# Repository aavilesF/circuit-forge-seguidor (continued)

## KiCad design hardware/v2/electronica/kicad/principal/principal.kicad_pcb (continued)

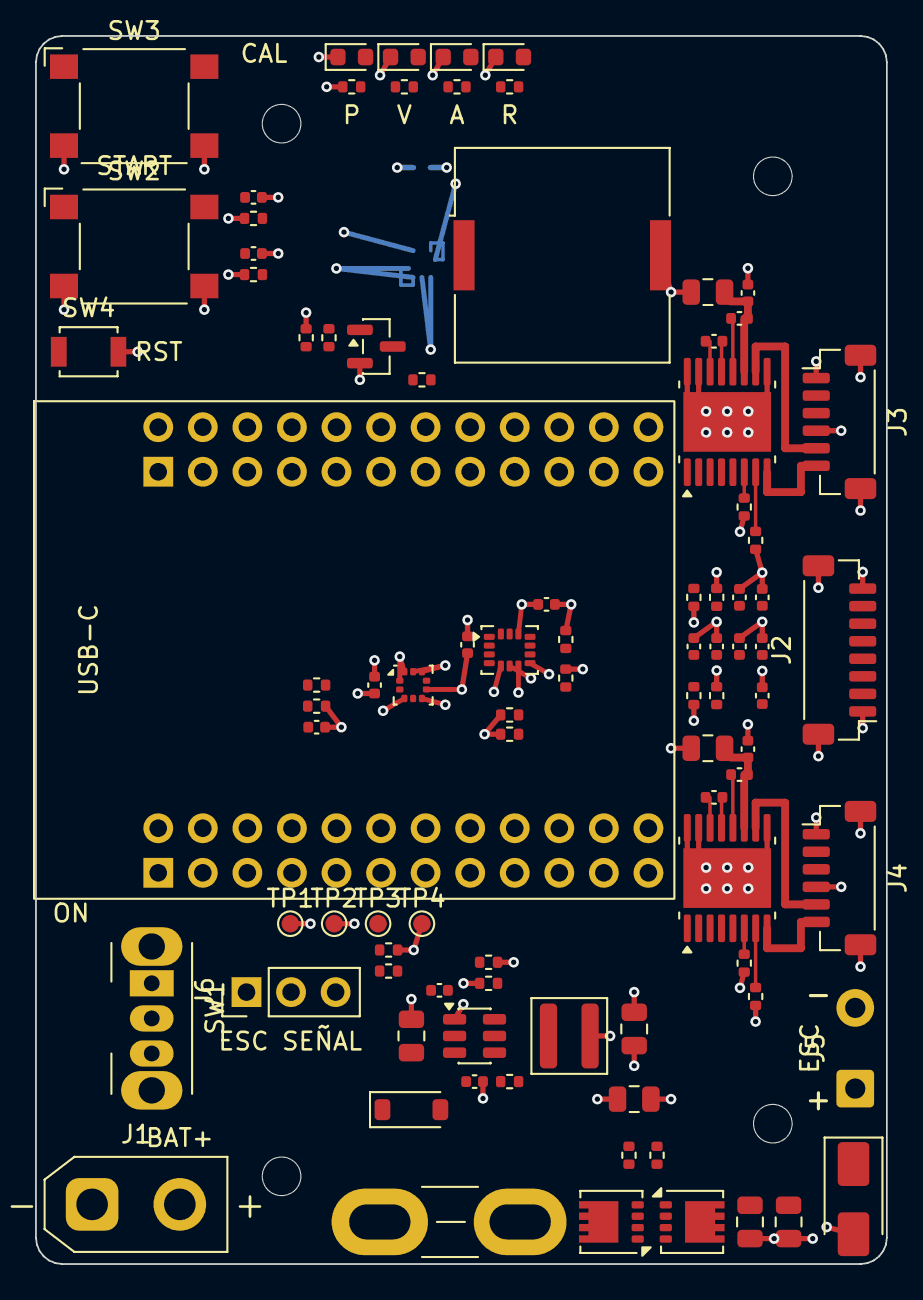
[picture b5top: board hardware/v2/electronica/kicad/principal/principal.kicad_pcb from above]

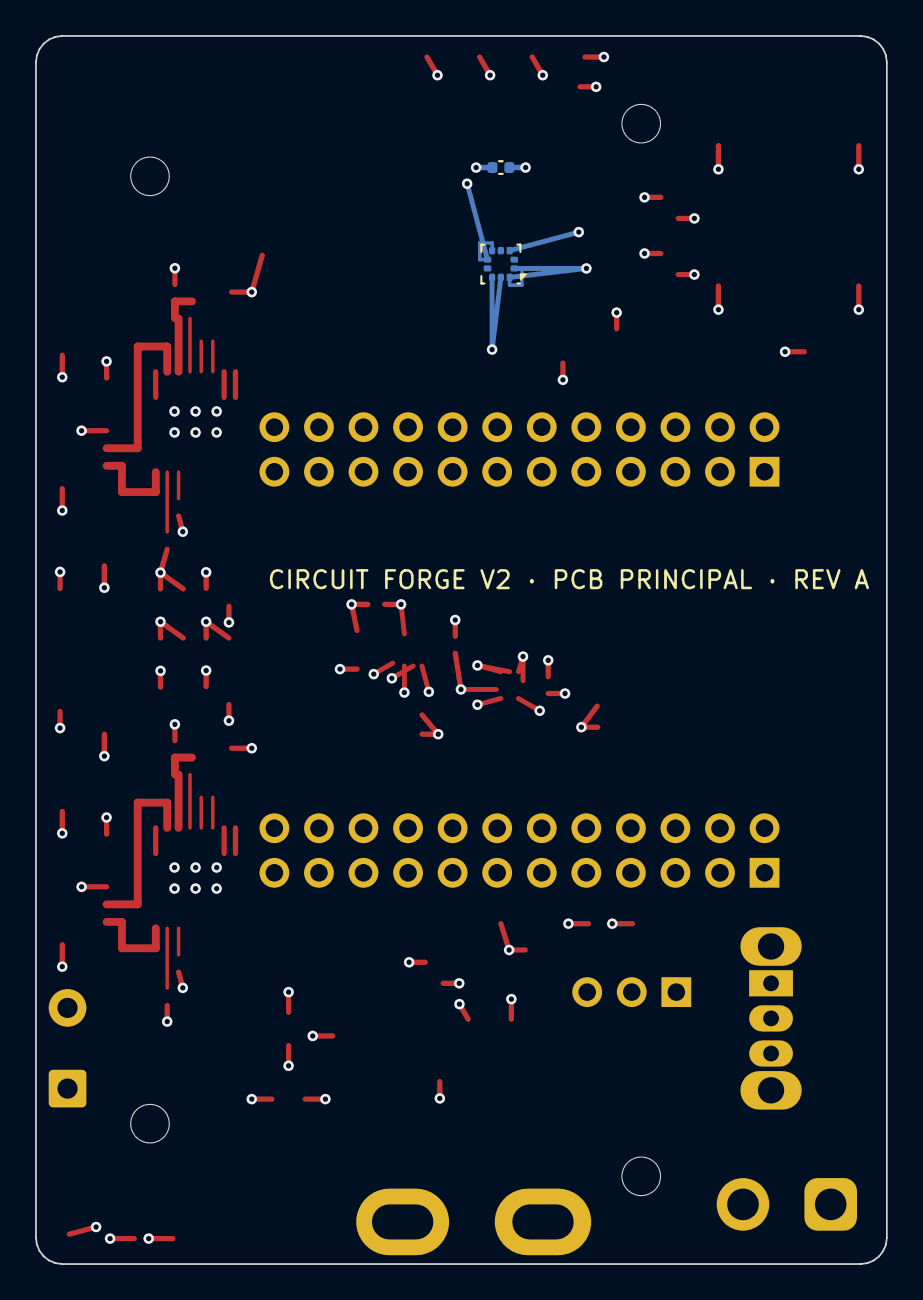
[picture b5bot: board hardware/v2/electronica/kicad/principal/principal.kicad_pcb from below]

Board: 4 copper layers, 48.5 x 70.0 mm, 96 parts (2 on the bottom side), 64 nets.

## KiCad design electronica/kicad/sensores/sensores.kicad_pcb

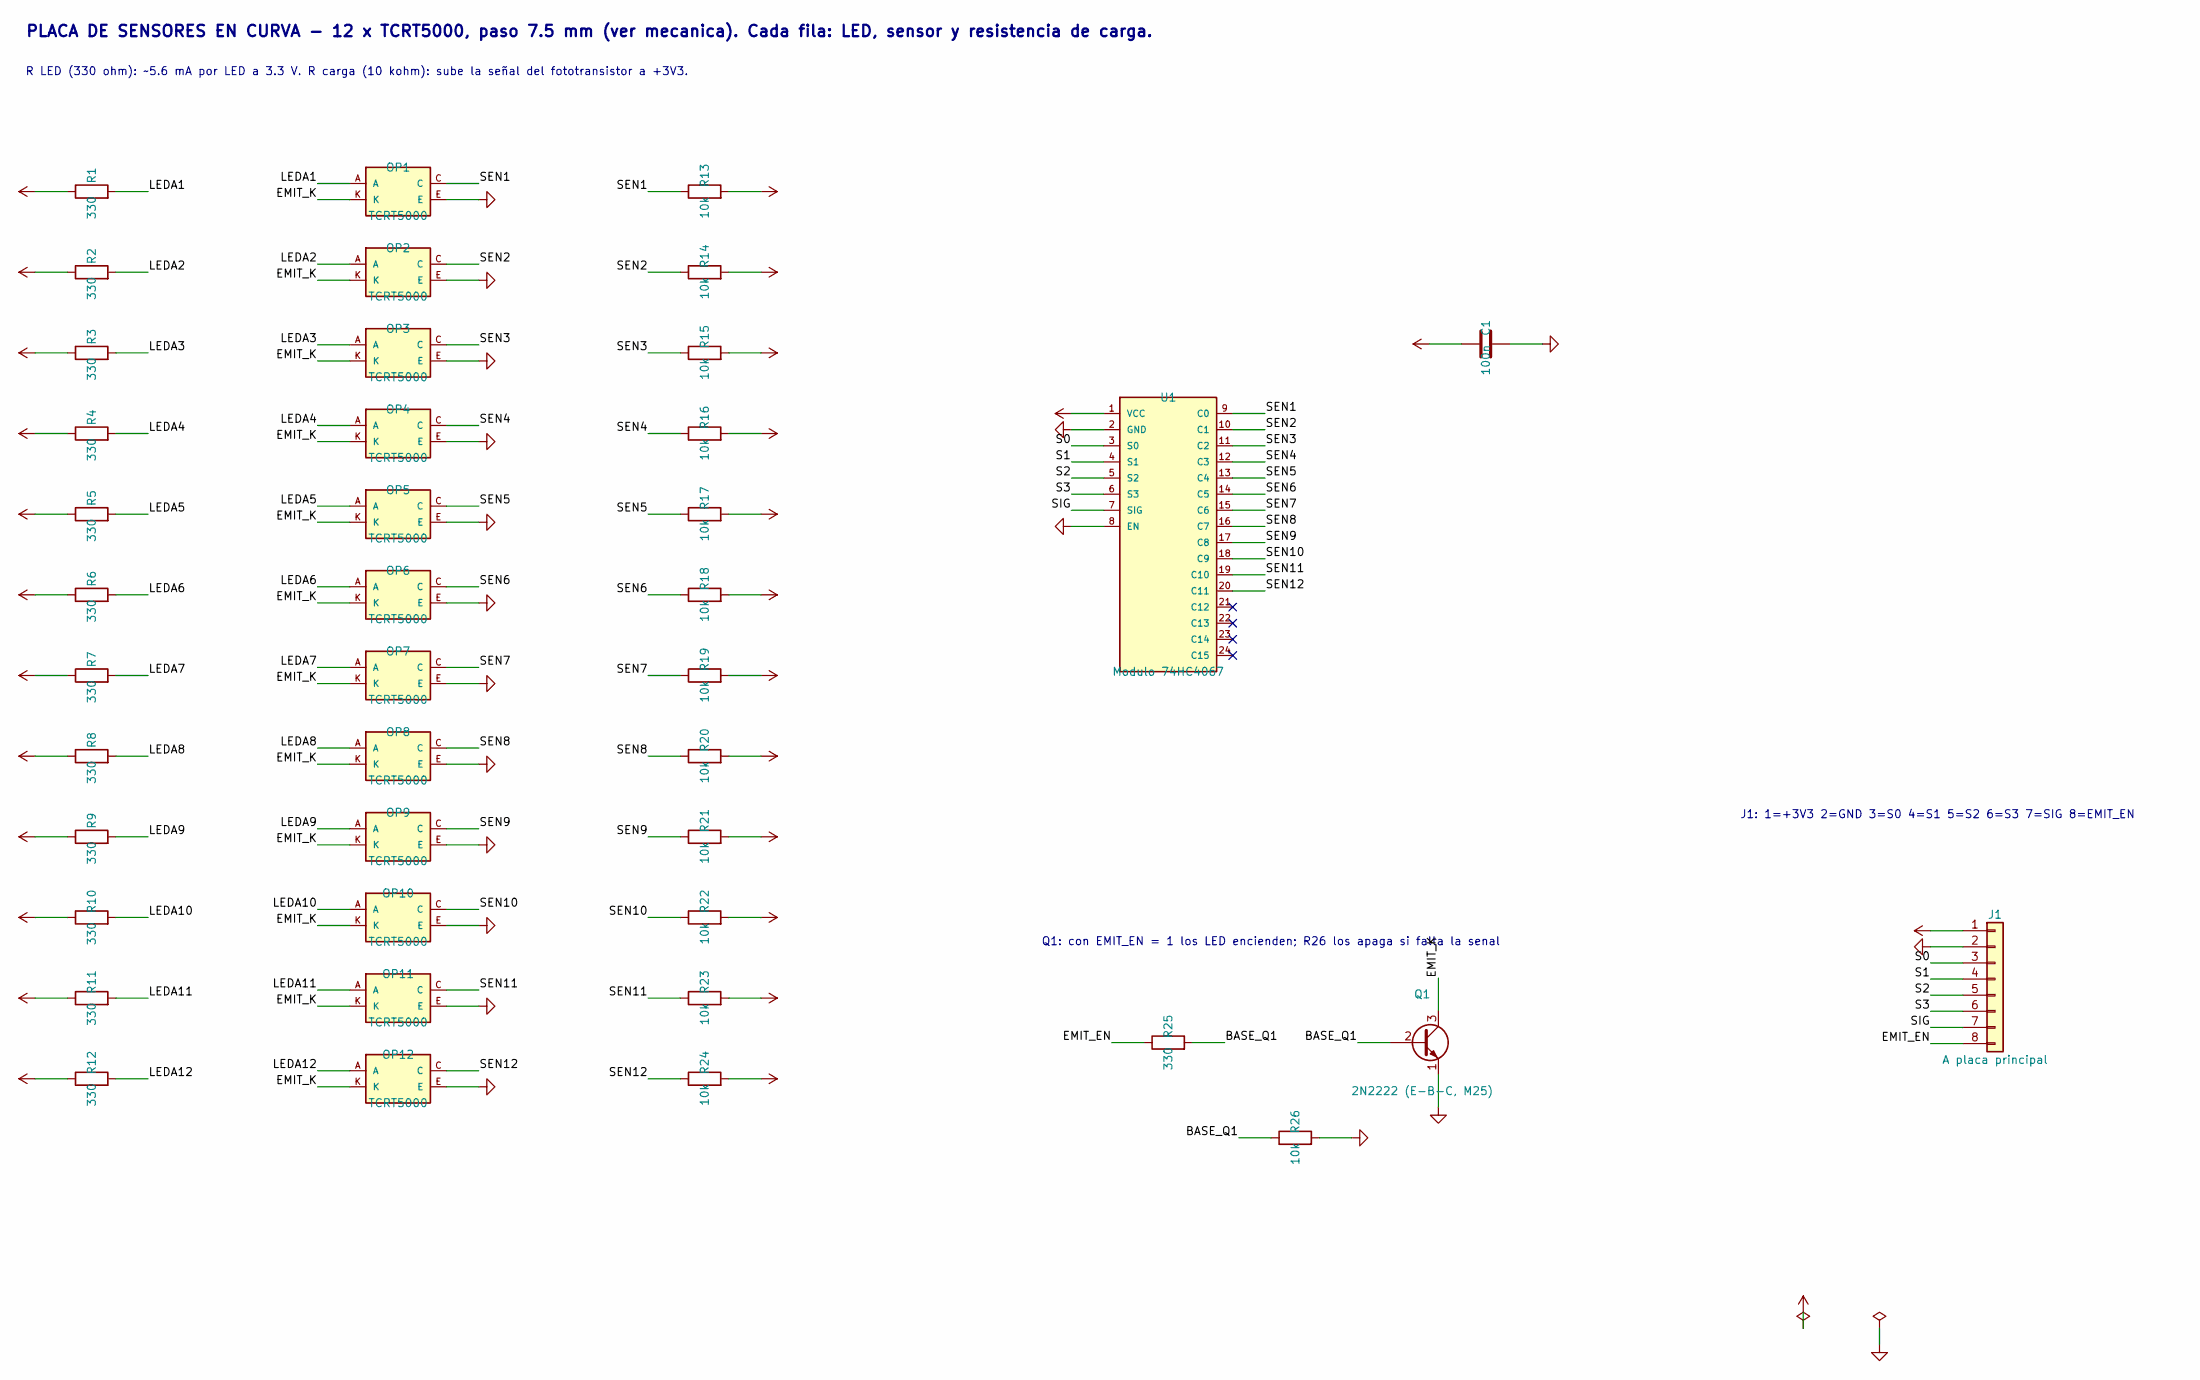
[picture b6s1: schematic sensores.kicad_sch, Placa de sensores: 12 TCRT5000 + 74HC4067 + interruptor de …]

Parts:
C1: 100n; C_Disc_D5.0mm_W2.5mm_P5.00mm
J1: A placa principal; PinHeader_1x08_P2.54mm_Vertical
OP1, OP2, OP3, OP4, OP5, OP6, OP7, OP8, OP9, OP10, OP11, OP12: TCRT5000; TCRT5000_THT
Q1: 2N2222 (E-B-C, M25); TO-92_Inline_Wide
R1, R2, R3, R4, R5, R6, R7, R8, R9, R10, R11, R12, R25: 330; R_Axial_DIN0207_L6.3mm_D2.5mm_P2.54mm_Vertical
R13, R14, R15, R16, R17, R18, R19, R20, R21, R22, R23, R24, R26: 10k; R_Axial_DIN0207_L6.3mm_D2.5mm_P2.54mm_Vertical
U1: Modulo 74HC4067; Modulo_MUX4067_VERIFICAR

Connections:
+3V3: C1.1, J1.1, R1.1, R2.1, R3.1, R4.1, R5.1, R6.1, R7.1, R8.1, R9.1, R10.1, R11.1, R12.1, R13.2, R14.2, R15.2, R16.2, R17.2, R18.2, R19.2, R20.2, R21.2, R22.2, R23.2, R24.2, U1.1 (VCC)
/BASE_Q1: Q1.2 (B), R25.2, R26.1
/EMIT_EN: J1.8, R25.1
/EMIT_K: OP1.K, OP2.K, OP3.K, OP4.K, OP5.K, OP6.K, OP7.K, OP8.K, OP9.K, OP10.K, OP11.K, OP12.K, Q1.3 (C)
/LEDA1: OP1.A, R1.2
/LEDA2: OP2.A, R2.2
/LEDA3: OP3.A, R3.2
/LEDA4: OP4.A, R4.2
/LEDA5: OP5.A, R5.2
/LEDA6: OP6.A, R6.2
/LEDA7: OP7.A, R7.2
/LEDA8: OP8.A, R8.2
/LEDA9: OP9.A, R9.2
/LEDA10: OP10.A, R10.2
/LEDA11: OP11.A, R11.2
/LEDA12: OP12.A, R12.2
/S0: J1.3, U1.3 (S0)
/S1: J1.4, U1.4 (S1)
/S2: J1.5, U1.5 (S2)
/S3: J1.6, U1.6 (S3)
/SEN1: OP1.C, R13.1, U1.9 (C0)
/SEN2: OP2.C, R14.1, U1.10 (C1)
/SEN3: OP3.C, R15.1, U1.11 (C2)
/SEN4: OP4.C, R16.1, U1.12 (C3)
/SEN5: OP5.C, R17.1, U1.13 (C4)
/SEN6: OP6.C, R18.1, U1.14 (C5)
/SEN7: OP7.C, R19.1, U1.15 (C6)
/SEN8: OP8.C, R20.1, U1.16 (C7)
/SEN9: OP9.C, R21.1, U1.17 (C8)
/SEN10: OP10.C, R22.1, U1.18 (C9)
/SEN11: OP11.C, R23.1, U1.19 (C10)
/SEN12: OP12.C, R24.1, U1.20 (C11)
/SIG: J1.7, U1.7 (SIG)
GND: C1.2, J1.2, OP1.E, OP2.E, OP3.E, OP4.E, OP5.E, OP6.E, OP7.E, OP8.E, OP9.E, OP10.E, OP11.E, OP12.E, Q1.1 (E), R26.2, U1.2 (GND), U1.8 (EN)

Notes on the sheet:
PLACA DE SENSORES EN CURVA - 12 x TCRT5000, paso 7.5 mm (ver mecanica). Cada fila: LED, sensor y resistencia de carga.
R LED (330 ohm): ~5.6 mA por LED a 3.3 V. R carga (10 kohm): sube la señal del fototransistor a +3V3.
Q1: con EMIT_EN = 1 los LED encienden; R26 los apaga si falta la senal
J1: 1=+3V3 2=GND 3=S0 4=S1 5=S2 6=S3 7=SIG 8=EMIT_EN

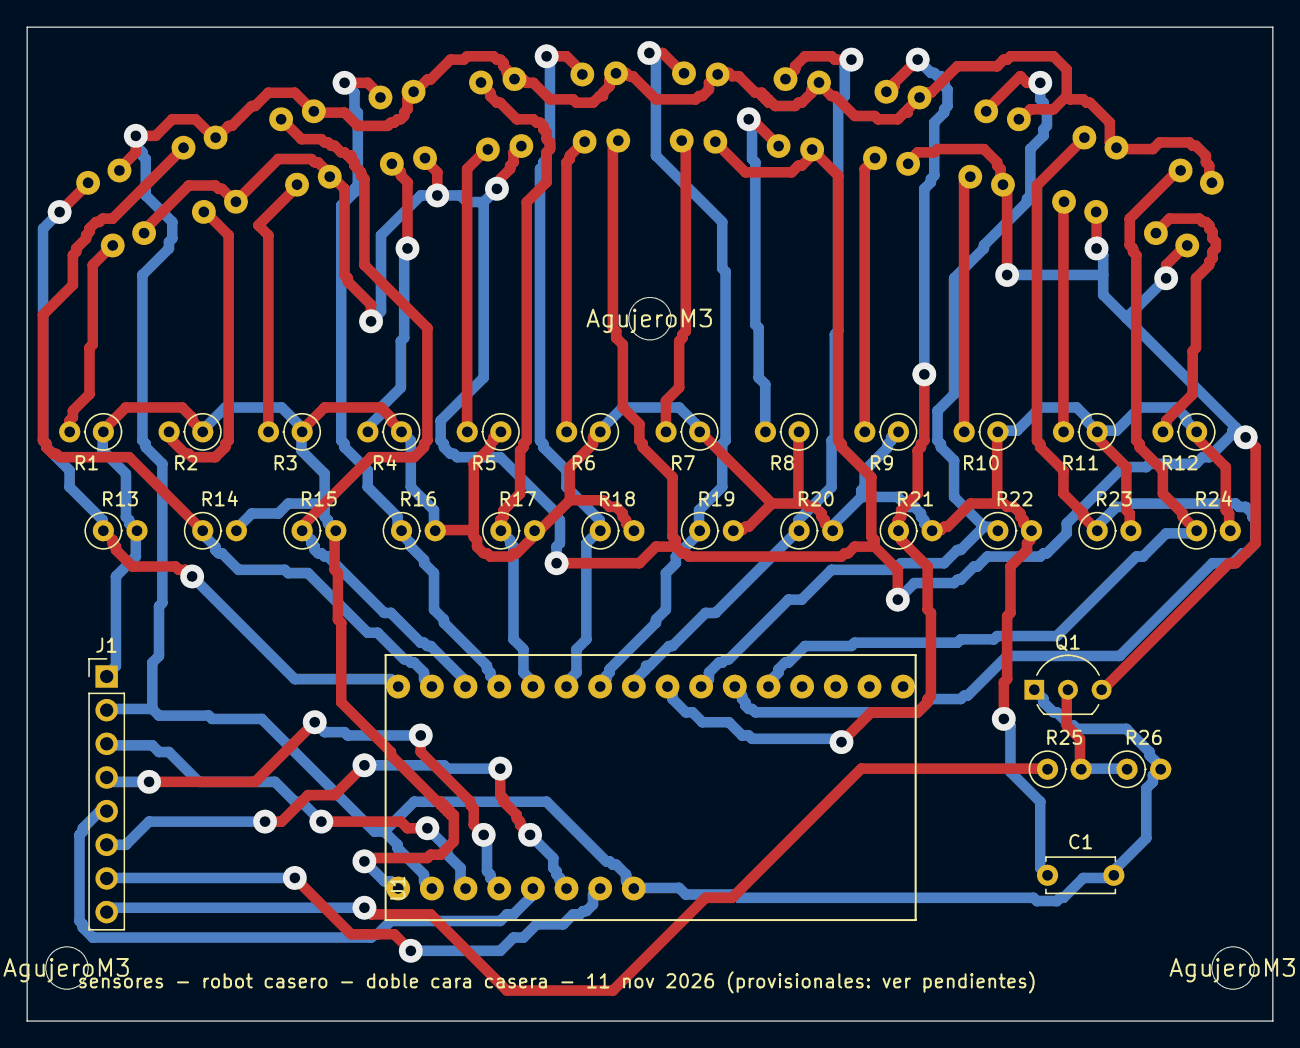
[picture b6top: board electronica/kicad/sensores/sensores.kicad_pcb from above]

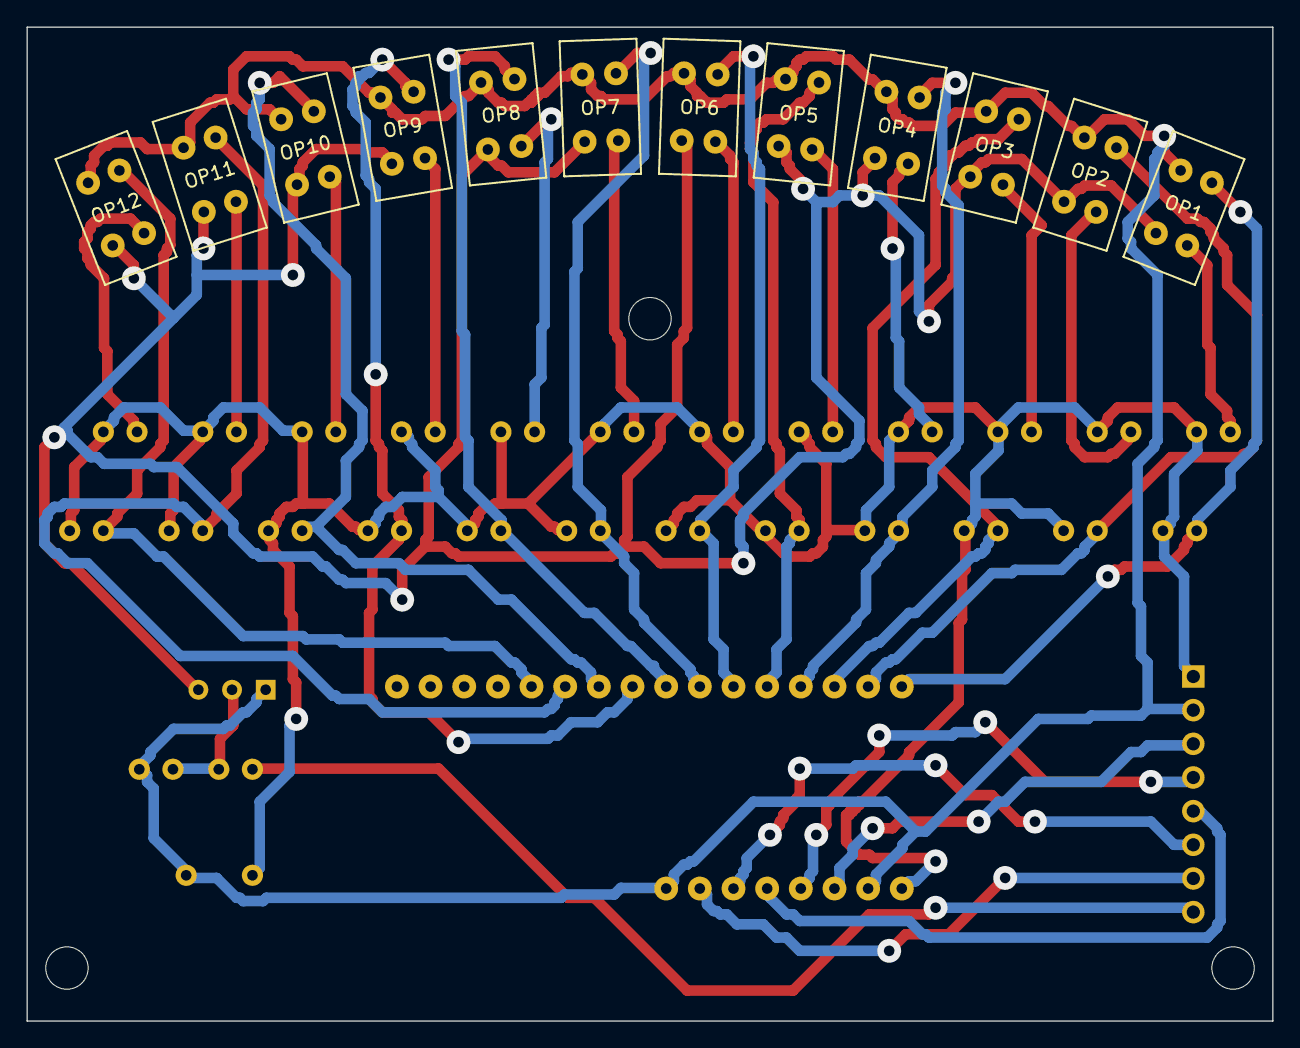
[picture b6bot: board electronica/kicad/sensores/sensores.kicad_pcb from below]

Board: 2 copper layers, 94.0 x 75.0 mm, 45 parts (12 on the bottom side), 34 nets.

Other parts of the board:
H1, H2, H3: AgujeroM3

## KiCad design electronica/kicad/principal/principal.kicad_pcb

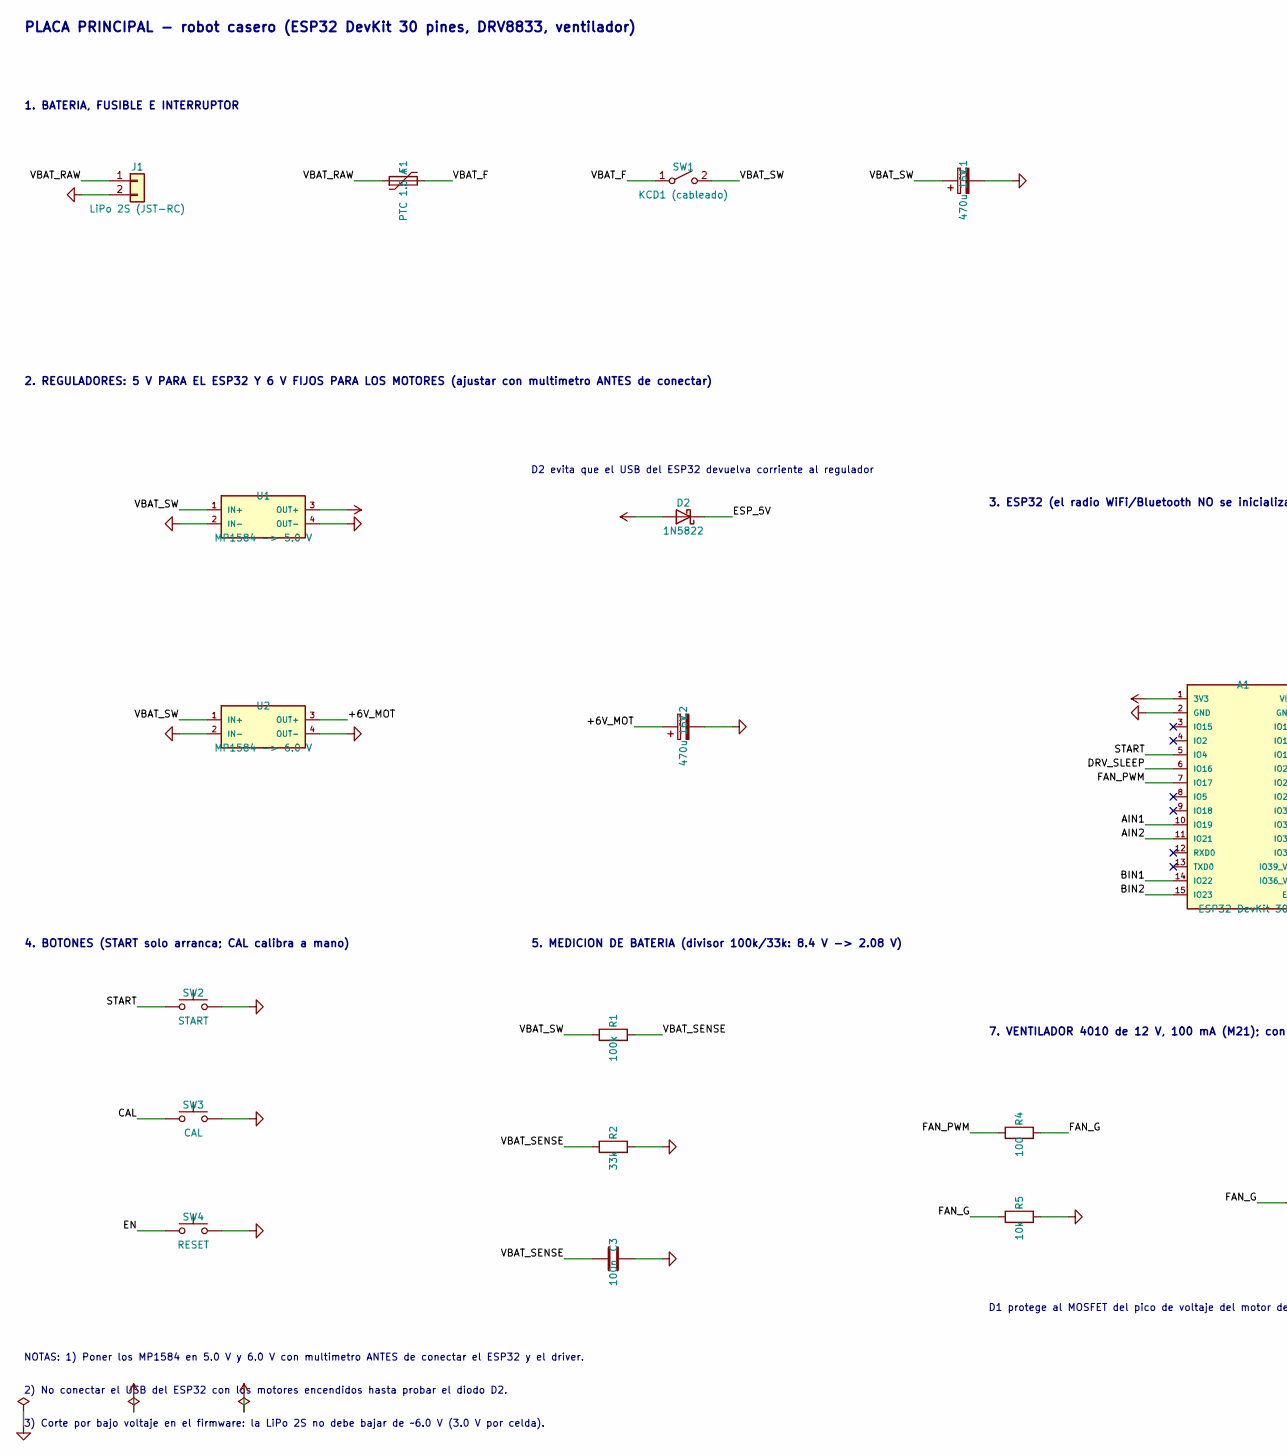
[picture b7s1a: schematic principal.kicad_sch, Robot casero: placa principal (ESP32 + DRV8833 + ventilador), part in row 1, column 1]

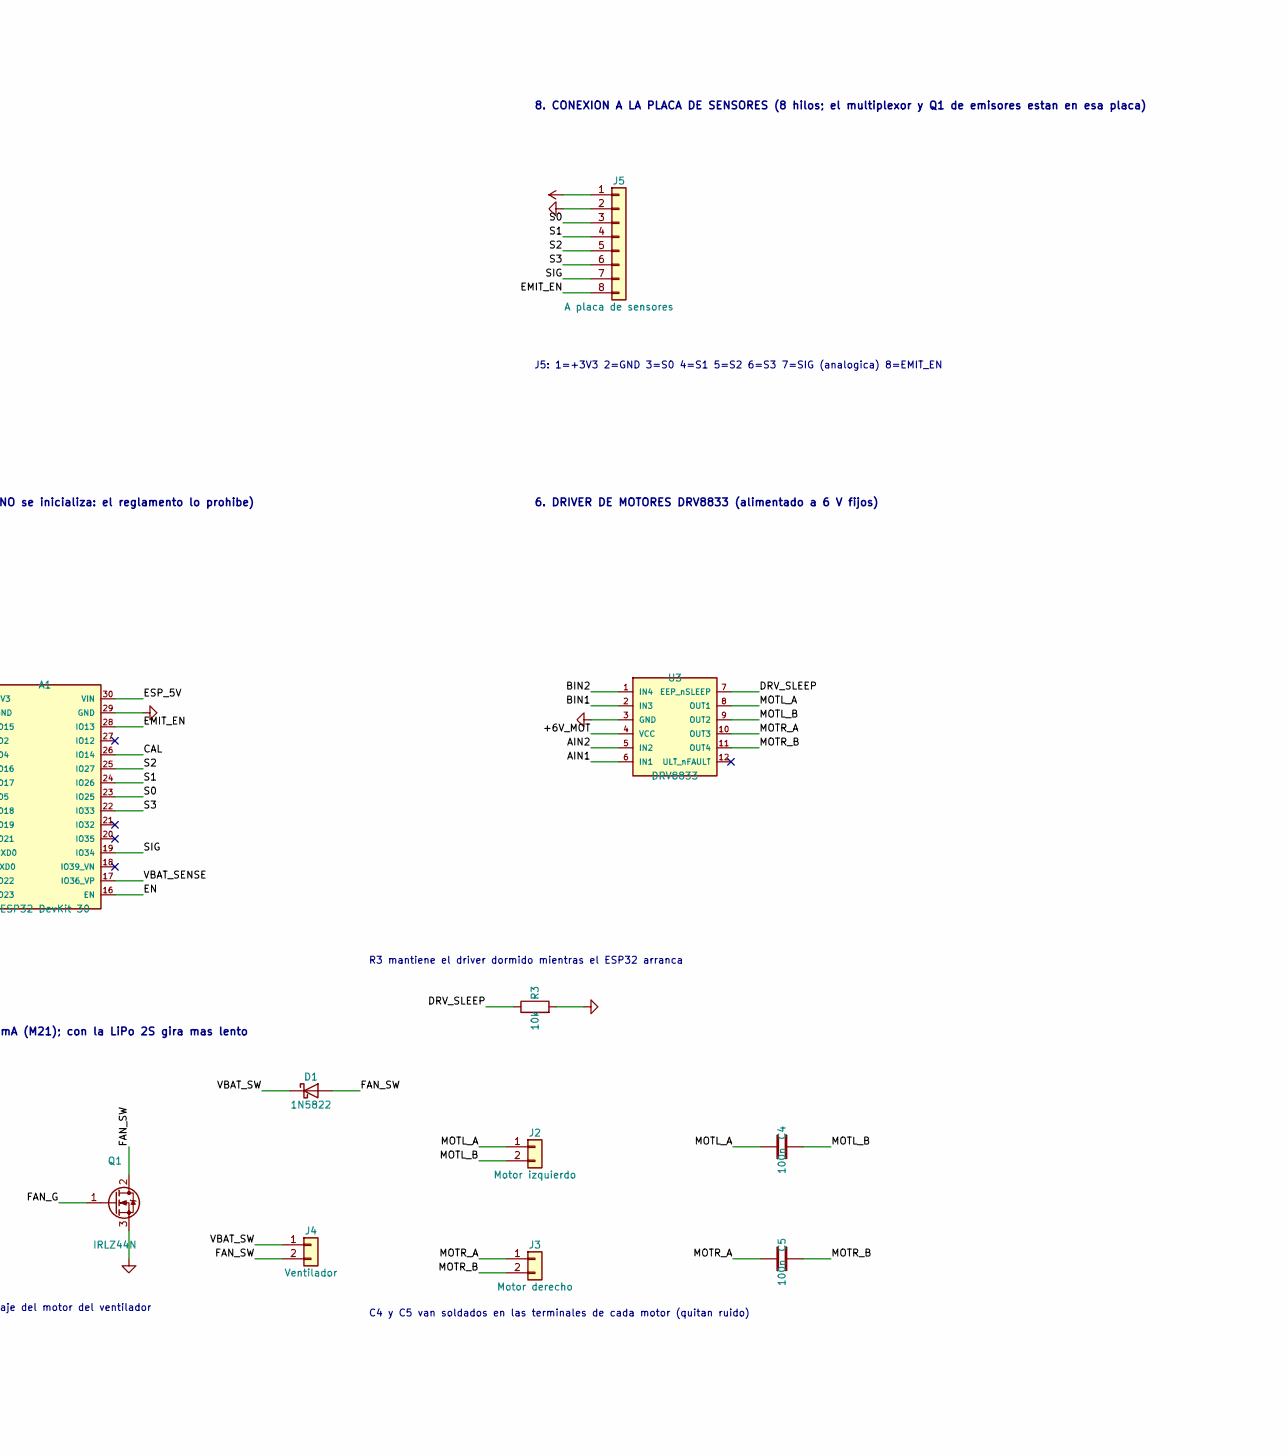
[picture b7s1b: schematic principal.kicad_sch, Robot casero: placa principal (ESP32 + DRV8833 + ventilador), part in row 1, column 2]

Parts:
A1: ESP32 DevKit 30; ESP32_DevKit_30
C1, C2: 470u 16V; CP_Radial_D8.0mm_P3.80mm
C3, C4, C5: 100n; C_Disc_D7.5mm_W5.0mm_P5.00mm
D1, D2: 1N5822; D_DO-201AD_P20.32mm_Taladro1.3
F1: PTC 1.5 A; PTC_Radial_VERIFICAR
J1: LiPo 2S (JST-RC); PinHeader_1x02_P2.54mm_Vertical
J2: Motor izquierdo; PinHeader_1x02_P2.54mm_Vertical
J3: Motor derecho; PinHeader_1x02_P2.54mm_Vertical
J4: Ventilador; PinHeader_1x02_P2.54mm_Vertical
J5: A placa de sensores; PinHeader_1x08_P2.54mm_Vertical
Q1: IRLZ44N; TO-220-3_Vertical
R1: 100k; R_Axial_DIN0207_L6.3mm_D2.5mm_P7.62mm_Horizontal
R2: 33k; R_Axial_DIN0207_L6.3mm_D2.5mm_P7.62mm_Horizontal
R3, R5: 10k; R_Axial_DIN0207_L6.3mm_D2.5mm_P7.62mm_Horizontal
R4: 100; R_Axial_DIN0207_L6.3mm_D2.5mm_P7.62mm_Horizontal
SW1: KCD1 (cableado); PinHeader_1x02_P2.54mm_Vertical
SW2: START; SW_PUSH-12mm
SW3: CAL; SW_PUSH_6mm
SW4: RESET; SW_PUSH_6mm
U1: MP1584 -> 5.0 V; Modulo_MP1584
U2: MP1584 -> 6.0 V; Modulo_MP1584
U3: DRV8833; Modulo_DRV8833

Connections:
+3V3: A1.1 (3V3), J5.1
+5V: D2.2 (A), U1.3 (OUT+)
/+6V_MOT: C2.1, U2.3 (OUT+), U3.4 (VCC)
/AIN1: A1.10 (IO19), U3.6 (IN1)
/AIN2: A1.11 (IO21), U3.5 (IN2)
/BIN1: A1.14 (IO22), U3.2 (IN3)
/BIN2: A1.15 (IO23), U3.1 (IN4)
/CAL: A1.26 (IO14), SW3.1
/DRV_SLEEP: A1.6 (IO16), R3.1, U3.7 (EEP_nSLEEP)
/EMIT_EN: A1.28 (IO13), J5.8
/EN: A1.16 (EN), SW4.1
/ESP_5V: A1.30 (VIN), D2.1 (K)
/FAN_G: Q1.1 (G), R4.2, R5.1
/FAN_PWM: A1.7 (IO17), R4.1
/FAN_SW: D1.2 (A), J4.2, Q1.2 (D)
/MOTL_A: C4.1, J2.1, U3.8 (OUT1)
/MOTL_B: C4.2, J2.2, U3.9 (OUT2)
/MOTR_A: C5.1, J3.1, U3.10 (OUT3)
/MOTR_B: C5.2, J3.2, U3.11 (OUT4)
/S0: A1.23 (IO25), J5.3
/S1: A1.24 (IO26), J5.4
/S2: A1.25 (IO27), J5.5
/S3: A1.22 (IO33), J5.6
/SIG: A1.19 (IO34), J5.7
/START: A1.5 (IO4), SW2.1
/VBAT_F: F1.2, SW1.1 (A)
/VBAT_RAW: F1.1, J1.1
/VBAT_SENSE: A1.17 (IO36_VP), C3.1, R1.2, R2.1
/VBAT_SW: C1.1, D1.1 (K), J4.1, R1.1, SW1.2 (B), U1.1 (IN+), U2.1 (IN+)
GND: A1.2 (GND), A1.29 (GND), C1.2, C2.2, C3.2, J1.2, J5.2, Q1.3 (S), R2.2, R3.2, R5.2, SW2.2, SW3.2, SW4.2, U1.2 (IN-), U1.4 (OUT-), U2.2 (IN-), U2.4 (OUT-), U3.3 (GND)

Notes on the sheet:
PLACA PRINCIPAL - robot casero (ESP32 DevKit 30 pines, DRV8833, ventilador)
1. BATERIA, FUSIBLE E INTERRUPTOR
2. REGULADORES: 5 V PARA EL ESP32 Y 6 V FIJOS PARA LOS MOTORES (ajustar con multimetro ANTES de conectar)
D2 evita que el USB del ESP32 devuelva corriente al regulador
3. ESP32 (el radio WiFi/Bluetooth NO se inicializa: el reglamento lo prohibe)
4. BOTONES (START solo arranca; CAL calibra a mano)
5. MEDICION DE BATERIA (divisor 100k/33k: 8.4 V -> 2.08 V)
6. DRIVER DE MOTORES DRV8833 (alimentado a 6 V fijos)
R3 mantiene el driver dormido mientras el ESP32 arranca
C4 y C5 van soldados en las terminales de cada motor (quitan ruido)
7. VENTILADOR 4010 de 12 V, 100 mA (M21); con la LiPo 2S gira mas lento
D1 protege al MOSFET del pico de voltaje del motor del ventilador
8. CONEXION A LA PLACA DE SENSORES (8 hilos; el multiplexor y Q1 de emisores estan en esa placa)
J5: 1=+3V3 2=GND 3=S0 4=S1 5=S2 6=S3 7=SIG (analogica) 8=EMIT_EN
NOTAS: 1) Poner los MP1584 en 5.0 V y 6.0 V con multimetro ANTES de conectar el ESP32 y el driver.
2) No conectar el USB del ESP32 con los motores encendidos hasta probar el diodo D2.
3) Corte por bajo voltaje en el firmware: la LiPo 2S no debe bajar de ~6.0 V (3.0 V por celda).

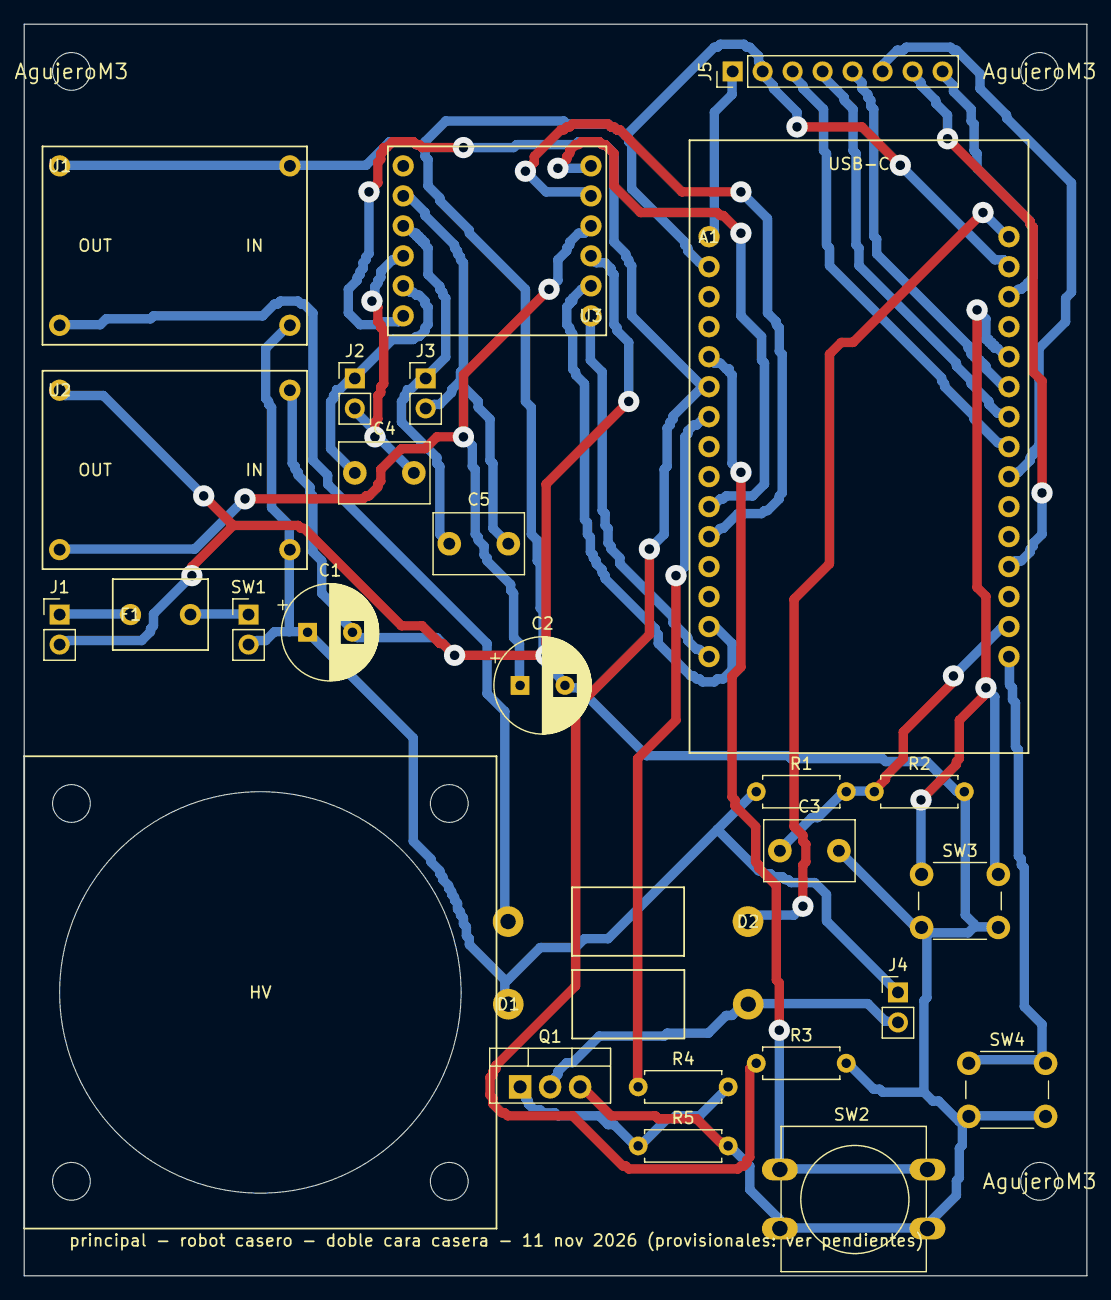
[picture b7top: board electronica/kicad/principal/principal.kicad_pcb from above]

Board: 2 copper layers, 90.0 x 106.0 mm, 31 parts (0 on the bottom side), 30 nets.

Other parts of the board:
H1, H2, H3: AgujeroM3
HV: Hueco ventilador; Hueco_Ventilador_34mm

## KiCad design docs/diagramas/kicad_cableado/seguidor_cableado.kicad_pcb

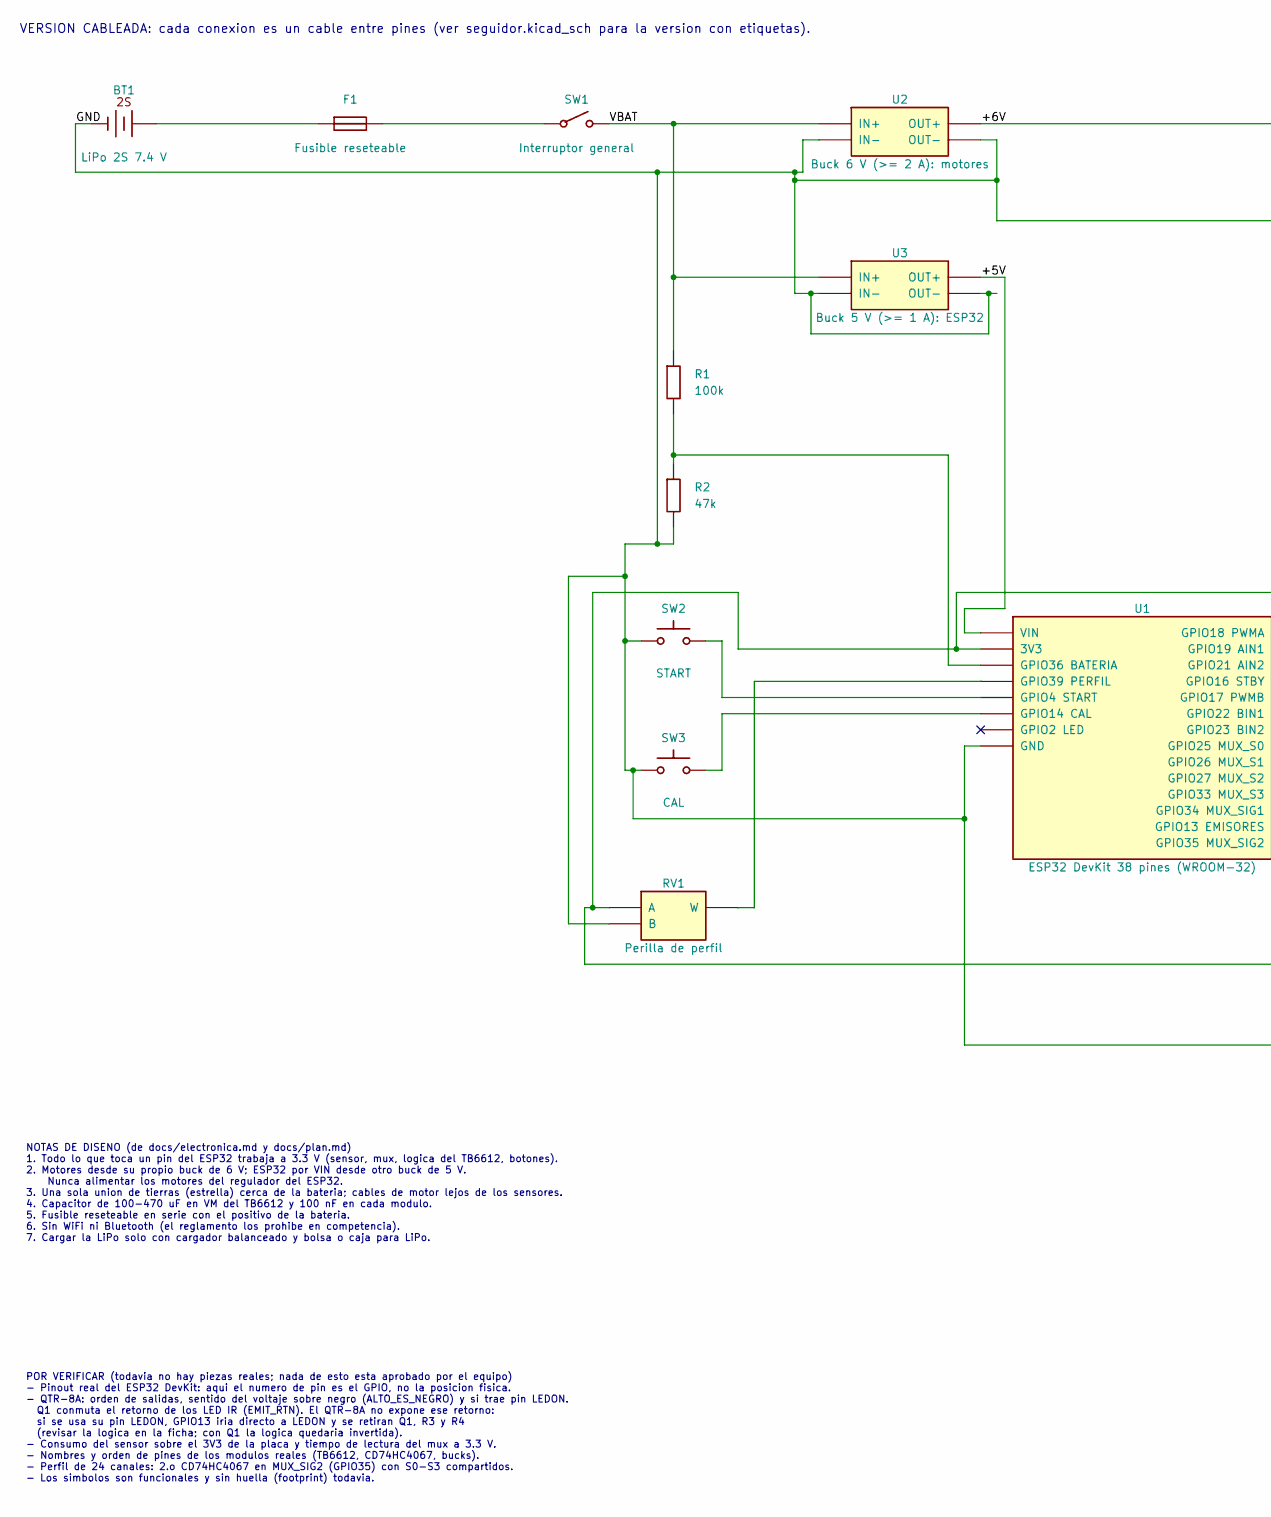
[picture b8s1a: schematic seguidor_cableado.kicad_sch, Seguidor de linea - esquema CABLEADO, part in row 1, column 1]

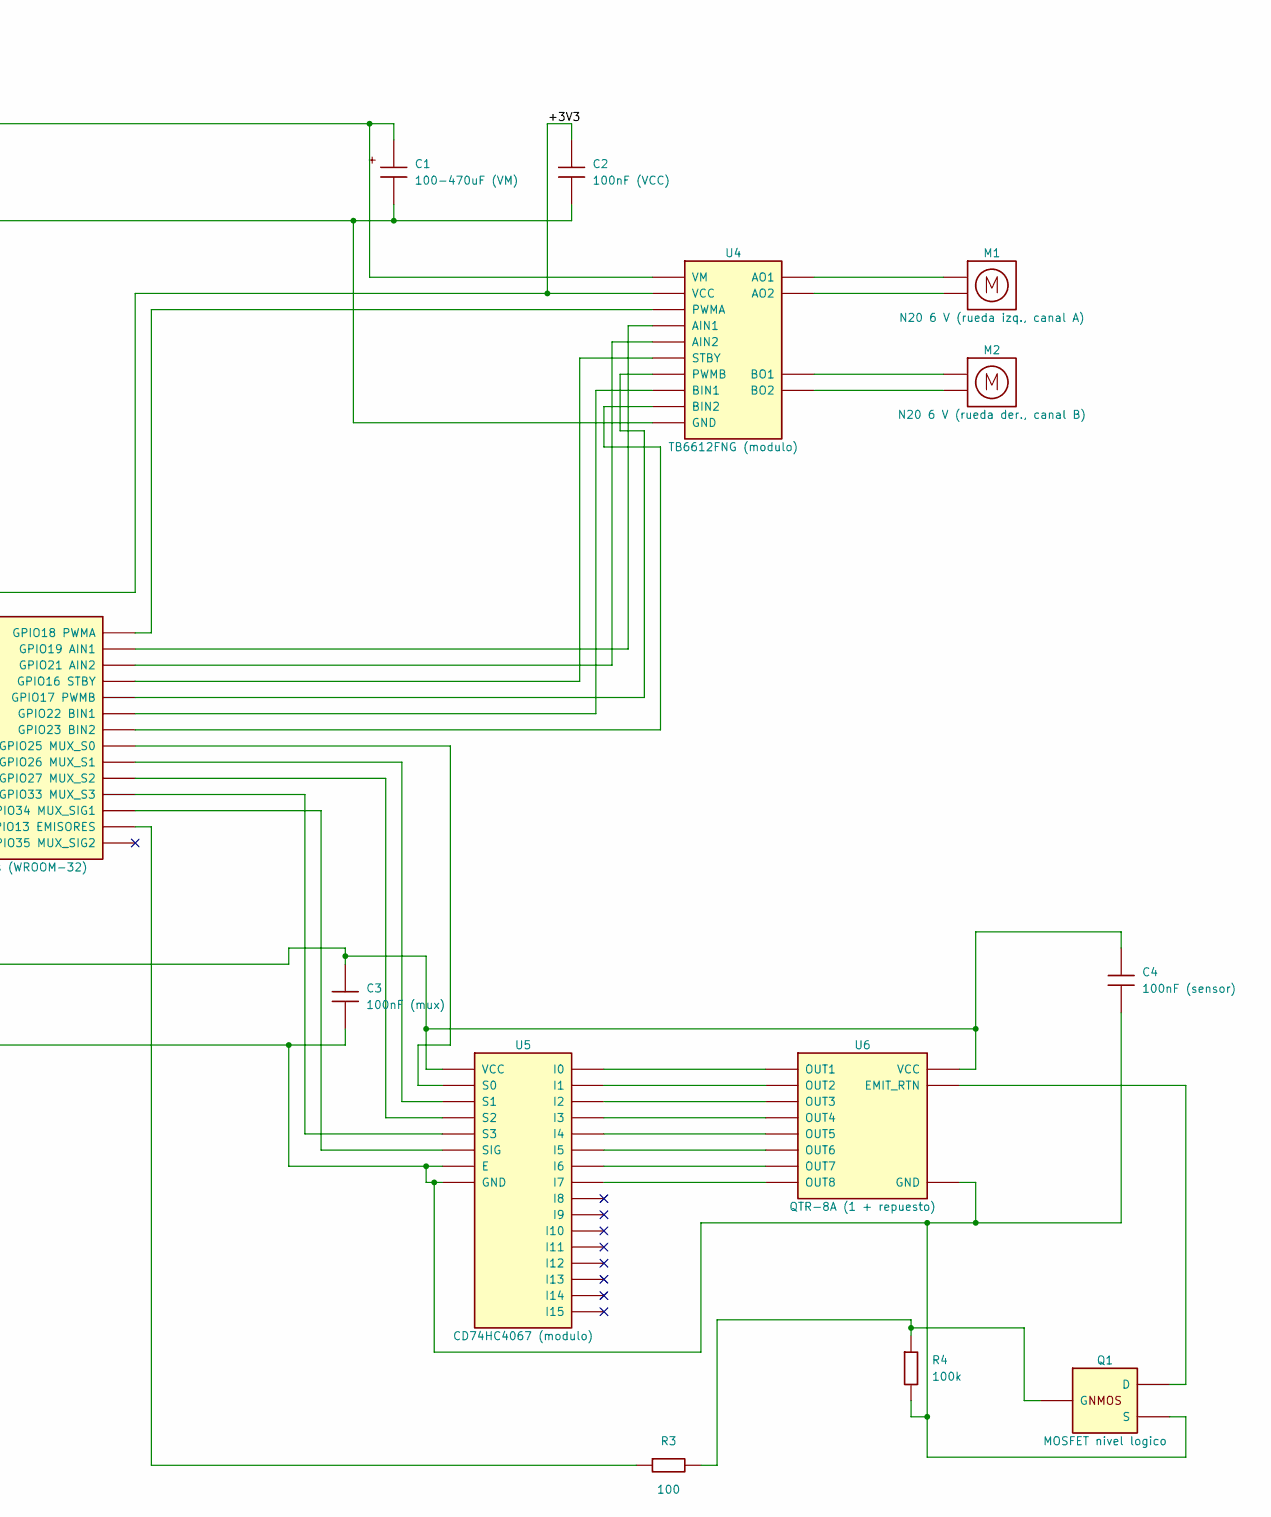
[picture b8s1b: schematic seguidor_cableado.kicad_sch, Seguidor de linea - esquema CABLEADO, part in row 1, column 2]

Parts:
BT1: LiPo 2S 7.4 V; Borne_2P_P5.0
C1: 100-470uF (VM); CP_Radial_D6.3_P2.5
C2: 100nF (VCC); C_Radial_P2.54
C3: 100nF (mux); C_Radial_P2.54
C4: 100nF (sensor); C_Radial_P2.54
F1: Fusible reseteable; PPTC_radial_P5.08
M1: N20 6 V (rueda izq., canal A); Cabecera_2P
M2: N20 6 V (rueda der., canal B); Cabecera_2P
Q1: MOSFET nivel logico; TO-92_MOSFET
R1, R4: 100k; R_Axial_P7.62
R2: 47k; R_Axial_P7.62
R3: 100; R_Axial_P7.62
RV1: Perilla de perfil; Cabecera_POT_1x3
SW1: Interruptor general; Cabecera_2P
SW2: START; SW_Tactil_6x6_TH
SW3: CAL; SW_Tactil_6x6_TH
U1: ESP32 DevKit 38 pines (WROOM-32); ESP32_DevKit_38
U2: Buck 6 V (>= 2 A): motores; Buck_modulo_4P
U3: Buck 5 V (>= 1 A): ESP32; Buck_modulo_4P
U4: TB6612FNG (modulo); TB6612FNG_modulo
U5: CD74HC4067 (modulo); CD74HC4067_modulo
U6: QTR-8A (1 + repuesto); Cabecera_QTR8A_1x11

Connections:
+3V3: C2.1, C3.1, C4.1, RV1.1 (A), U1.3V3, U4.2 (VCC), U5.7 (VCC), U6.9 (VCC)
+5V: U1.VIN, U3.3 (OUT+)
+6V: C1.1 (+), U2.3 (OUT+), U4.1 (VM)
AIN1: U1.19 (GPIO19 AIN1), U4.5 (AIN1)
AIN2: U1.21 (GPIO21 AIN2), U4.6 (AIN2)
BATERIA: R1.2, R2.1, U1.36 (GPIO36 BATERIA)
BIN1: U1.22 (GPIO22 BIN1), U4.9 (BIN1)
BIN2: U1.23 (GPIO23 BIN2), U4.10 (BIN2)
CAL: SW3.1, U1.14 (GPIO14 CAL)
EMISORES: R3.1, U1.13 (GPIO13 EMISORES)
EMIT_RTN: Q1.3 (D), U6.11 (EMIT_RTN)
GND: BT1.1 (-), C1.2 (-), C2.2, C3.2, C4.2, Q1.1 (S), R2.2, R4.2, RV1.2 (B), SW2.2, SW3.2, U1.GND, U2.2 (IN-), U2.4 (OUT-), U3.2 (IN-), U3.4 (OUT-), U4.3 (GND), U5.5 (E), U5.8 (GND), U6.10 (GND)
MOT_DER_1: M2.1, U4.13 (BO1)
MOT_DER_2: M2.2, U4.14 (BO2)
MOT_IZQ_1: M1.1, U4.11 (AO1)
MOT_IZQ_2: M1.2, U4.12 (AO2)
MUX_S0: U1.25 (GPIO25 MUX_S0), U5.1 (S0)
MUX_S1: U1.26 (GPIO26 MUX_S1), U5.2 (S1)
MUX_S2: U1.27 (GPIO27 MUX_S2), U5.3 (S2)
MUX_S3: U1.33 (GPIO33 MUX_S3), U5.4 (S3)
MUX_SIG1: U1.34 (GPIO34 MUX_SIG1), U5.6 (SIG)
PERFIL: RV1.3 (W), U1.39 (GPIO39 PERFIL)
PWMA: U1.18 (GPIO18 PWMA), U4.4 (PWMA)
PWMB: U1.17 (GPIO17 PWMB), U4.8 (PWMB)
Q1_G: Q1.2 (G), R3.2, R4.1
SENS1: U5.9 (I0), U6.1 (OUT1)
SENS2: U5.10 (I1), U6.2 (OUT2)
SENS3: U5.11 (I2), U6.3 (OUT3)
SENS4: U5.12 (I3), U6.4 (OUT4)
SENS5: U5.13 (I4), U6.5 (OUT5)
SENS6: U5.14 (I5), U6.6 (OUT6)
SENS7: U5.15 (I6), U6.7 (OUT7)
SENS8: U5.16 (I7), U6.8 (OUT8)
START: SW2.1, U1.4 (GPIO4 START)
STBY: U1.16 (GPIO16 STBY), U4.7 (STBY)
VBAT: R1.1, SW1.2, U2.1 (IN+), U3.1 (IN+)
VBAT_BAT: BT1.2 (+), F1.1
VBAT_FUS: F1.2, SW1.1

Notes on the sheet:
NOTAS DE DISENO (de docs/electronica.md y docs/plan.md) 1. Todo lo que toca un pin del ESP32 trabaja a 3.3 V (sensor, mux, logica del TB6612, botones). 2. Motores desde su propio buck de 6 V; ESP32 por VIN desde otro buck de 5 V. Nunca alimentar los motores del regulador del ESP32. 3. Una sola unio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
POR VERIFICAR (todavia no hay piezas reales; nada de esto esta aprobado por el equipo) - Pinout real del ESP32 DevKit: aqui el numero de pin es el GPIO, no la posicion fisica. - QTR-8A: orden de salidas, sentido del voltaje sobre negro (ALTO_ES_NEGRO) y si trae pin LEDON. Q1 conmuta el retorno de l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
VERSION CABLEADA: cada conexion es un cable entre pines (ver seguidor.kicad_sch para la version con etiquetas).
